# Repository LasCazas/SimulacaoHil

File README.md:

<p align="center">
  
</p>

<h1 align="center">Simulador Dinâmico HIL — Speeduino 48-Way</h1>

<p align="center">
  <b>Bancada Hardware-in-the-Loop orientada ao condutor (Logitech G29 / Sliders Virtuais + ESP32 DevKit V1 + KTM Duke 390)</b><br/>
  <i>Instituto Federal de Minas Gerais (IFMG) — Campus Betim · Equipe IF Betim Racing</i>
</p>

<p align="center">

</p>

---

## Visão Geral

Este repositório reúne o firmware embarcado, a interface gráfica de controle/telemetria, a modelagem física parametrizável em JSON e a documentação técnica em LaTeX da **Bancada de Simulação Dinâmica HIL** da equipe **IF Betim Racing**.

O sistema permite validar mapas de injeção/ignição, estratégias de partida, corte de giro e malha fechada da **Speeduino 48-Way** em bancada antes de levar a calibração para a pista, simulando em tempo real a planta completa de uma **KTM Duke 390** (~373 cm³, monocilíndrica, roda fônica **22-2**):

- **Modo Duplo de Pilotagem e HUD Estilo Fórmula 1 (`interface_g29.py`):** exibe o volante oficial da equipe girando em tempo real, colunas verticais de pedais interativas estilo telemetria de Fórmula 1 (`ACEL`, `FREIO`, `EMB`) e indicador central de marcha com 15 LEDs de *Shift Light* — operando tanto com o **Logitech G29 real** quanto pelo **Modo Simulado na Interface** (clique/arraste no volante e nos pedais ou digite a porcentagem exata).
- **Áudio "Berrador" em Tempo Real no PC (`berrador_audio.py`):** sintetiza o ronco do motor diretamente na placa de som do computador (sem ocupar o ESP32 nem exigir um segundo DAC I2S), com *pitch-shifting* contínuo, *crossfade* de faixas, corte de giro e *pops & bangs* na desaceleração.
- **Planta Dinâmica em Tempo Real no ESP32 (`HIL_Esp/HIL_Esp.ino`):** integra a cada `0,5 ms` a inércia do virabrequim, curva de torque WOT, atrito interno, marcha lenta, acoplamento progressivo de embreagem, câmbio de 6 marchas (+ ré virtual de bancada), arrasto aerodinâmico, resistência ao rolamento e freios — gerando um sinal **VSS** com decaimento inercial fiel à motocicleta real.
- **Roda Fônica 22-2 via DMA/I2S (`PCM5102A`):** síntese senoidal contínua de 44,1 kHz sem travar o laço principal da física.
- **Parametrização Quente sem Regravar (`moto_duke390.json`):** altere cilindrada, inércia, vazão de bico, massa, relações de marcha ou curva de torque no JSON e envie via Serial com um clique.

---

## Links Importantes (Documentação & Mapa Base)

| Recurso | Acesso |
|---|---|
| **Documentação Técnica Completa (PDF)** | [**`SimulacaoComG29_ComOPCEEsp.pdf`**](./SimulacaoComG29_ComOPCEEsp.pdf) *(fontes LaTeX em [`SimulacaoComG29_ComOPCEEsp/`](./SimulacaoComG29_ComOPCEEsp/))* |
| **Mapa Base Oficial (`.msq`) e Configurações do TunerStudio** | [**Acessar Pasta Oficial no Google Drive**](https://drive.google.com/drive/folders/1bbK6THQXaumvtmB5yQu2AqLAyRcFz2Z0) |

> **Importante:** O arquivo `.msq` disponível no Google Drive já entrega toda a configuração base da **Speeduino 48-Way** pronta para a bancada (decodificador de roda fônica `22-2`, portas de entrada/saída, calibração inicial de sensores e tabelas base de VE e avanço).

---

## Arquitetura do Sistema HIL

<p align="center">
  
</p>

1. **Interface Humana (PC — Python/Tkinter @ 30 Hz):** lê o Logitech G29 via `pygame` *ou* os sliders manuais de `0%` a `100%`, transmite comandos à razão de `115200 bps` pela porta COM e exibe o painel de telemetria em tempo real (`RPM`, `km/h`, `VSS Hz`, `Torque Nm`, `MAP kPa`, `Pulso de Injeção µs`, `Fator de Combustível` e `Ignição`).
2. **Planta Física (ESP32 DevKit V1 — 30 pinos):** converte as variáveis do modelo em tensões analógicas (`DAC1` e `DAC2` filtrados por RC), frequência variável (`PWM LEDC` para o `VSS`), nível digital (`Clutch_in`) e onda fônica diferencial/AC (`I2S -> PCM5102A`).
3. **Fechamento de Malha (Speeduino $\rightarrow$ Conversor de Nível Lógico $\rightarrow$ ISRs do ESP32):** captura por interrupção de hardware a largura de pulso do bico injetor (`INJ-1-OUT`) e o disparo da centelha (`IGN-1-OUT`).

---

## Mapeamento de Pinos (ESP32 DevKit V1 $\leftrightarrow$ Speeduino 48-Way)

Para preservar os dois conversores analógicos internos de 8 bits do ESP32 (`GPIO 25` e `GPIO 26`) dedicados ao **TPS** e ao **MAP**, os pinos de relógio do módulo **I2S PCM5102A** foram alocados em `GPIO 27` e `GPIO 14`:

| Sinal Simulado / Lido | Pino ESP32 | Tipo de Sinal | Condicionamento / Módulo | Conector Speeduino |
|---|---|---|---|---|
| **TPS** (Acelerador) | `GPIO 25` | `DAC1` (0–3,3 V) | Filtro RC ($10\text{ k}\Omega + 1\,\mu\text{F}$ p/ `GND`) | `B_C7` (`TPS_Sensor`) |
| **MAP** (Pressão Coletor) | `GPIO 26` | `DAC2` (0–3,3 V) | Filtro RC ($10\text{ k}\Omega + 1\,\mu\text{F}$ p/ `GND`) | `B_C8` (`MAP-EXT`) |
| **Crank 22-2** (`BCK`) | `GPIO 27` | `I2S BCK` | Pino `BCK` do PCM5102A | `B_B2` (`CRANK-IN`) |
| **Crank 22-2** (`LCK`) | `GPIO 14` | `I2S WS/LCK` | Pino `LCK` do PCM5102A | *(saída de áudio `L` do PCM5102A)* |
| **Crank 22-2** (`DIN`) | `GPIO 22` | `I2S DATA` | Pino `DIN` do PCM5102A | `B_B3` (`VR1-` $\leftarrow$ `GND` PCM5102A) |
| **Velocidade** (`VSS`) | `GPIO 16` | `PWM LEDC` | Direto ($0\text{--}3{,}3\text{ V}$, proporcional a $v$) | `B_A7` (`VSS`) |
| **Embreagem** | `GPIO 15` | Saída Digital | Direto ($0\text{--}3{,}3\text{ V}$) | `B_B7` (`Clutch_in`) |
| **Retorno Bico 1** | `GPIO 4` | `ISR (CHANGE)` | Conversor de Nível Lógico (`Chan2`: `HV` $\rightarrow$ `LV`) | `G_A1` (`INJ-1-OUT`) |
| **Retorno Bobina 1** | `GPIO 5` | `ISR (RISING)` | Conversor de Nível Lógico (`Chan1`: `HV` $\rightarrow$ `LV`) | `G_B1` (`IGN-1-OUT`) |
| **Referência Comum** | `GND` | Terra Lógico | Unificar `GND` do ESP32, PCM5102A, Conversor e ECU | `B_A8` (`GND Sensores`) |

### Configuração Obrigatória dos Pinos do Módulo PCM5102A
Para a placa roxa GY-PCM5102A funcionar sem entrar em mudo e com relógio interno ativo:
* **`VCC`**: Ligar no pino **`VIN (5V)`** do ESP32.
* **`GND`**: Ligar no **`GND`** do ESP32.
* **`SCK` (ou SCL)**: **OBRIGATÓRIO ligar no `GND`** (ativa o PLL interno para gerar o master clock a partir do BCK).
* **`XMT` (ou XSMT)**: **OBRIGATÓRIO ligar no `3.3V`** (desativa o Soft Mute de fábrica; se ficar solto a placa fica 100% muda).
* **`FMT`**: Ligar no **`GND`** (seleciona formato I2S padrão).
* **`FLT` e `DMP`**: Ligar no **`GND`** (filtro normal e sem de-ênfase).

### Condicionamento sem Bico e sem Bobina Físicos (Level Converter)

<p align="center">
  
</p>

Como na bancada HIL **não conectamos bico injetor nem bobina de ignição reais**, não existem cargas indutivas nem surtos de alta tensão (*flyback*). Assim, um **Módulo Conversor de Nível Lógico Bidirecional** (MOSFET BSS138 com resistores de *pull-up* de $10\text{ k}\Omega$ integrados) realiza toda a leitura de retorno com total segurança para o ESP32 ($3{,}3\text{ V}$):

- **Alimentação do módulo:** `HV = 5V`, `LV = 3.3V` (do ESP32) e `GND` comum.
- **Injeção (`G_A1 — INJ-1-OUT` $\rightarrow$ Canal 2 $\rightarrow$ `GPIO 4`):** a saída de injetor da Speeduino é *Low-Side* (dreno aberto). O próprio resistor de *pull-up* de $10\text{ k}\Omega$ do lado `HV` faz o papel de carga virtual segura: mantém `3,3 V` em repouso no `GPIO 4` e cai instantaneamente a `0 V` durante o tempo exato de abertura do bico.
- **Ignição (`G_B1 — IGN-1-OUT` $\rightarrow$ Canal 1 $\rightarrow$ `GPIO 5`):** converte o pulso lógico de `5 V` (*Smart Coil*) da ECU para `3,3 V` limpos na entrada de interrupção do ESP32.

---

## Estrutura de Arquivos

```text
SimulacaoHil/
├── HIL_Esp/
│   └── HIL_Esp.ino                       # Firmware principal do ESP32 DevKit V1 (física + I2S + DAC + ISRs)
├── CodigoEsp/
│   └── CodigoEsp.ino                     # Código base histórico (gerador isolado da roda fônica 22-2)
├── SimulacaoComG29_ComOPCEEsp/
│   ├── SimulacaoComG29_ComOPCEEsp.tex    # Código-fonte LaTeX da documentação técnica
│   └── images/                           # Logos, diagrama HIL e foto do conversor de nível lógico
├── interface_g29.py                      # Interface gráfica Tkinter (Modo G29 Real + Modo Sliders 0-100%)
├── moto_duke390.json                     # Parâmetros físicos documentados da KTM Duke 390
├── config_g29.json                       # Preferências salvas automaticamente pela interface
├── requirements.txt                      # Dependências Python (pygame, pyserial)
└── SimulacaoComG29_ComOPCEEsp.pdf        # Documentação técnica compilada pronta para leitura
```

---

## Como Reproduzir Passo a Passo

### 1. Carregar o Mapa Base na Speeduino
1. Baixe o arquivo `.msq` na [pasta oficial do Google Drive](https://drive.google.com/drive/folders/1bbK6THQXaumvtmB5yQu2AqLAyRcFz2Z0) e abra no **TunerStudio**.
2. Como os DACs nativos do ESP32 excursionam de `0 V` a `3,3 V`, faça a calibração rápida de **TPS** no TunerStudio (*Tools $\rightarrow$ Calibrate TPS*) usando `0%` e `100%` pela própria interface Python.

### 2. Gravar o ESP32 DevKit V1
1. Abra [`HIL_Esp/HIL_Esp.ino`](./HIL_Esp/HIL_Esp.ino) na **Arduino IDE** (com o pacote *esp32 by Espressif Systems* instalado).
2. Selecione a placa **`ESP32 Dev Module`** e faça o upload via USB.

### 3. Executar a Interface no PC
```powershell
git clone https://github.com/LasCazas/SimulacaoHil.git
cd SimulacaoHil

python -m venv .venv
.\.venv\Scripts\activate
pip install -r requirements.txt

python interface_g29.py
```

### 4. Operar (Com ou Sem Volante G29)
- Selecione a **Porta COM** do ESP32 e clique em **Conectar** (após `2 s`, os parâmetros de `moto_duke390.json` são carregados automaticamente no ESP32).
- Escolha em **Modo de Controle**:
  - **Volante Real (Logitech G29):** lê pedais, volante, câmbio H (1ª a 6ª + Ré) e borboletas. Ajuste os números dos eixos ou `inv` se necessário — tudo fica salvo em `config_g29.json` ao fechar a janela.
  - **Simulado na Interface (Barrinhas % / Manual):** arraste os sliders ou digite a porcentagem exata de `0%` a `100%` (ótimo para estabilizar pontos específicos de carga/RPM durante o acerto do mapa!) e clique nos botões de marcha `R`, `N`, `1..6`.
- Para ativar a realimentação em malha fechada pelo pulso real do bico da Speeduino, mude `"use_inj_feedback"` para `1` em [`moto_duke390.json`](./moto_duke390.json) e clique em **Reenviar parâmetros**.

---

<p align="center">
  
  <br/>
  <sub>Desenvolvido por <b>William Las-Cazas Queiroz</b> — Gerente Técnico (Equipe Elétrica · IF Betim Racing)</sub>
</p>

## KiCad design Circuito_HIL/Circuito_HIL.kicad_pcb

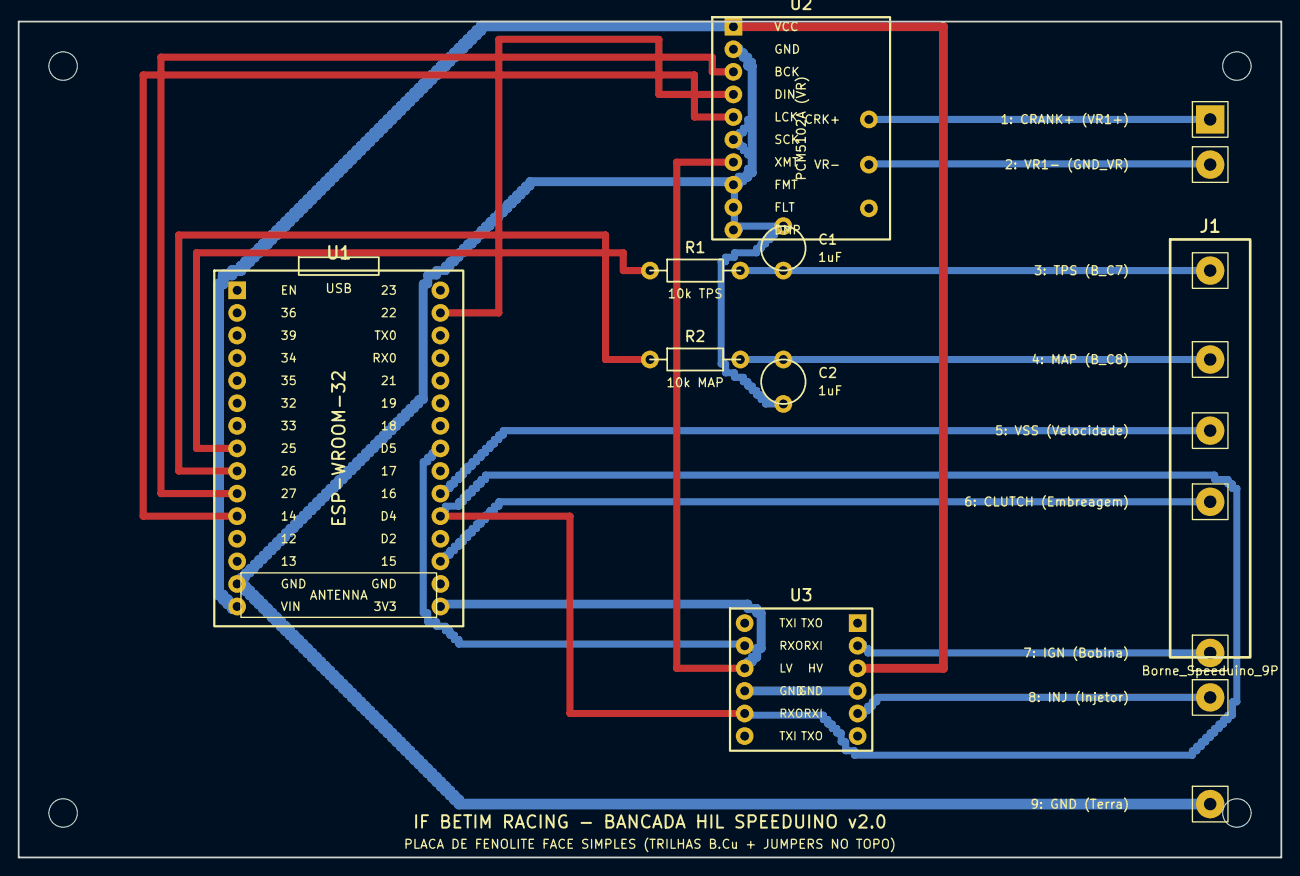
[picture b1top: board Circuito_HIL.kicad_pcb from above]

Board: 2 copper layers, 142.0 x 94.0 mm, 8 parts (0 on the bottom side), 18 nets.

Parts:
C1, C2: 1uF; C_Disc_D5.0mm_W2.5mm_P5.00mm
J1: Borne_Speeduino_9P; TerminalBlock_Phoenix_MKDS-1,5-9-5.08_1x09_P5.08mm_Horizont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
R1: 10k TPS; R_Axial_DIN0207_L6.3mm_D2.5mm_P10.16mm_Horizontal
R2: 10k MAP; R_Axial_DIN0207_L6.3mm_D2.5mm_P10.16mm_Horizontal
U1: ESP32_DevKit_V1; ESP32_DevKit_V1_30Pin
U2: GY-PCM5102A; GY_PCM5102A
U3: Level_Converter; Logic_Level_Converter_4CH

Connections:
+3V3: U1.16, U2.7, U3.9
+5V: U1.15, U2.1, U3.3
/CLUTCH_SIG: J1.6, U1.18
/CRANK_VR_NEG: J1.2, U2.12
/CRANK_VR_POS: J1.1, U2.11
/FB_IGN_3V3: U1.23, U3.8
/FB_INJ_3V3: U1.20, U3.11
/I2S_BCK: U1.10, U2.3
/I2S_DIN: U1.29, U2.4
/I2S_LCK: U1.11, U2.5
/NET_MAP_OUT: C2.1, J1.4, R2.1
/NET_TPS_OUT: C1.1, J1.3, R1.1
/SPEEDUINO_IGN: J1.7, U3.2
/SPEEDUINO_INJ: J1.8, U3.5
/VSS_PULSE: J1.5, U1.21
GND: C1.2, C2.2, J1.9, U1.14, U1.17, U2.2, U2.6, U2.8, U2.9, U2.10, U3.4, U3.10
unnamed: R1.2, U1.8
unnamed: R2.2, U1.9

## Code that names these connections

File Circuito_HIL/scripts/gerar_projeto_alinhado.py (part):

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    sch.append('\t(label "NET_MAP_OUT" (at 45.0 125.00 180) (effects (font (size 1.27 1.27)) (justify right)))')
    sch.append('\t(label "NET_MAP_OUT" (at 290.0 102.46 180) (effects (font (size 1.27 1.27)) (justify right)))')

    sch.append('\t(label "I2S_BCK" (at 88.0 106.68 180) (effects (font (size 1.27 1.27)) (justify right)))')
    sch.append('\t(label "I2S_BCK" (at 190.0 58.65 180) (effects (font (size 1.27 1.27)) (justify right)))')

    sch.append('\t(label "I2S_LCK" (at 88.0 109.22 180) (effects (font (size 1.27 1.27)) (justify right)))')
    sch.append('\t(label "I2S_LCK" (at 190.0 63.73 180) (effects (font (size 1.27 1.27)) (justify right)))')

    sch.append('\t(label "I2S_DIN" (at 142.0 86.36 0) (effects (font (size 1.27 1.27)) (justify left)))')
    sch.append('\t(label "I2S_DIN" (at 190.0 61.19 180) (effects (font (size 1.27 1.27)) (justify right)))')

    sch.append('\t(label "CRANK_VR_POS" (at 240.0 58.65 0) (effects (font (size 1.27 1.27)) (justify left)))')
    sch.append('\t(label "CRANK_VR_POS" (at 290.0 94.84 180) (effects (font (size 1.27 1.27)) (justify right)))')

    sch.append('\t(label "CRANK_VR_NEG" (at 240.0 63.73 0) (effects (font (size 1.27 1.27)) (justify left)))')
    sch.append('\t(label "CRANK_VR_NEG" (at 290.0 97.38 180) (effects (font (size 1.27 1.27)) (justify right)))')

    sch.append('\t(label "VSS_PULSE" (at 142.0 106.68 0) (effects (font (size 1.27 1.27)) (justify left)))')
    sch.append('\t(label "VSS_PULSE" (at 290.0 105.00 180) (effects (font (size 1.27 1.27)) (justify right)))')

    sch.append('\t(label "CLUTCH_SIG" (at 142.0 116.84 0) (effects (font (size 1.27 1.27)) (justify left)))')
    sch.append('\t(label "CLUTCH_SIG" (at 290.0 107.54 180) (effects (font (size 1.27 1.27)) (justify right)))')

    sch.append('\t(label "SPEEDUINO_IGN" (at 190.0 143.73 180) (effects (font (size 1.27 1.27)) (justify right)))')
    sch.append('\t(label "SPEEDUINO_IGN" (at 290.0 112.62 180) (effects (font (size 1.27 1.27)) (justify right)))')

    sch.append('\t(label "FB_IGN_3V3" (at 240.0 143.73 0) (effects (font (size 1.27 1.27)) (justify left)))')
    sch.append('\t(label "FB_IGN_3V3" (at 142.0 101.60 0) (effects (font (size 1.27 1.27)) (justify left)))')

    sch.append('\t(label "SPEEDUINO_INJ" (at 190.0 148.81 180) (effects (font (size 1.27 1.27)) (justify right)))')
    sch.append('\t(label "SPEEDUINO_INJ" (at 290.0 110.08 180) (effects (font (size 1.27 1.27)) (justify right)))')

    sch.append('\t(label "FB_INJ_3V3" (at 240.0 148.81 0) (effects (font (size 1.27 1.27)) (justify left)))')
    sch.append('\t(label "FB_INJ_3V3" (at 142.0 109.22 0) (effects (font (size 1.27 1.27)) (justify left)))')

    # ================= WIRES =================
    
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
